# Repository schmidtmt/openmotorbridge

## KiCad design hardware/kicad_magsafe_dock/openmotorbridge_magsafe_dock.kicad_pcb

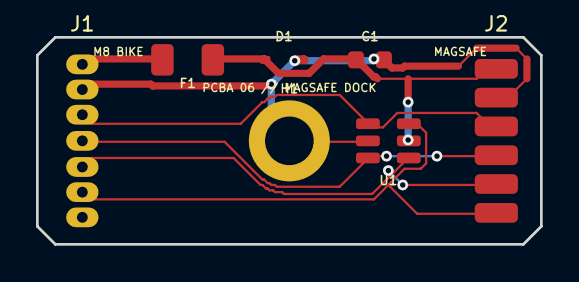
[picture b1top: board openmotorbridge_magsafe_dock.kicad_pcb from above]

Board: 2 copper layers, 28.0 x 11.5 mm, 7 parts (0 on the bottom side), 7 nets.

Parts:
C1: 100nF; C_0603_1608Metric
D1: ESD5Z5.0; D_SOD-323
F1: 500mA_PPTC; Fuse_1206_3216Metric
H1: M2.5_MOUNT_HOLE; MountingHole_2.7mm_M2.5_Pad
J1: M8_6P_WIRE_PADS; SolderWirePad_1x07_SMD_2.0mm
J2: MAGSAFE_6P_DOCK; PinHeader_1x06_P2.54mm_Vertical_SMD_Pin1Left
U1: USBLC6-4SC6; SOT-23-6

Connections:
1WIRE_ID: J1.6, J2.6, U1.6
GND: C1.2, D1.2, H1.1, J1.2, J2.2, U1.2
SIG_N: J1.4, J2.4, U1.3
SIG_P: J1.3, J2.3, U1.1
TRIGGER_PPS: J1.5, J2.5, U1.4
VCC_IN: F1.1, J1.1
VCC_PROT: C1.1, D1.1, F1.2, J2.1, U1.5

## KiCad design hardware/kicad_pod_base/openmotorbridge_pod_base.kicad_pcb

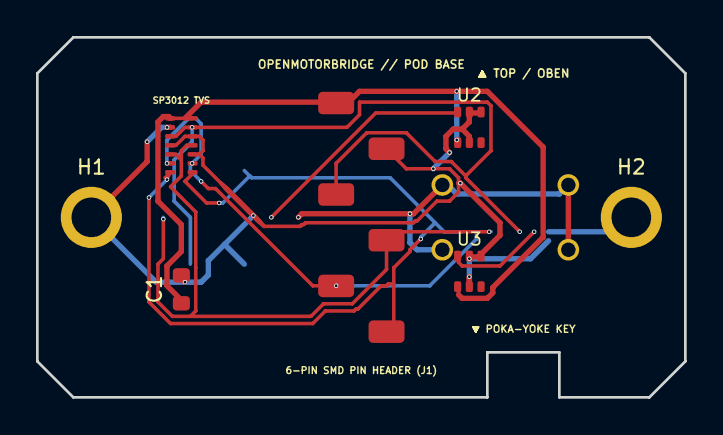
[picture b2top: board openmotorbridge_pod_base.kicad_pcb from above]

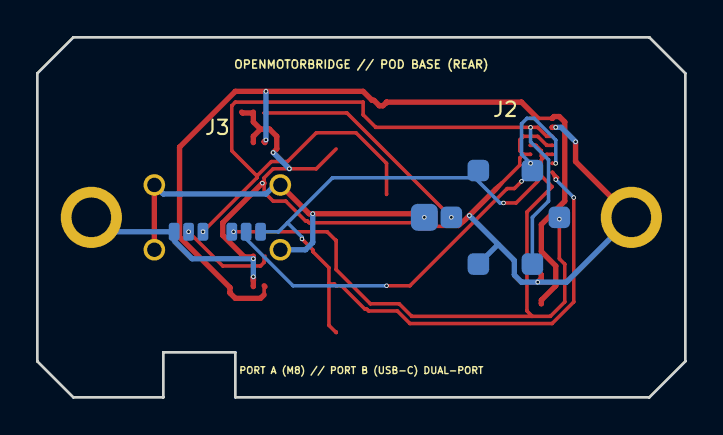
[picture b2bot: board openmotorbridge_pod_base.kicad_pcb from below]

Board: 2 copper layers, 36.0 x 20.0 mm, 9 parts (2 on the bottom side), 9 nets.

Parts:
C1: 100nF_50V; C_0603_1608Metric
H1, H2: M2_MountingHole; MountingHole_2.2mm_M2_Pad
J1: MILL_MAX_824_SMD_6P; PinHeader_1x06_P2.54mm_Vertical_SMD_Pin1Left
J2: PORT_A_M8_6PIN; M8_6Pin_IP67_Receptacle_Socketed
J3: PORT_B_USBC_VERTICAL; USB_C_Receptacle_Vertical_6P
U1: SP3012-06UTG; DFN-14_1.35x3.5mm_P0.5mm
U2: LM66100_PORTA; SOT-363_SC-70-6
U3: LM66100_PORTB; SOT-363_SC-70-6

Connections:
1WIRE_ID: J1.6, J2.6, J3.6, U1.7, U1.8
GND: C1.2, H1.1, H2.1, J1.2, J2.2, J3.1, U1.2, U1.4, U1.10, U1.12, U2.2, U2.3, U2.5, U3.2, U3.3, U3.5
GND_SHIELD: J2.7, J3.SH
SIG_N: J1.4, J2.4, J3.4, U1.5, U1.11
SIG_P: J1.3, J2.3, J3.3, U1.3, U1.13
TRIGGER_PPS: J1.5, J2.5, J3.5, U1.6, U1.9
VCC: C1.1, J1.1, U1.1, U1.14, U2.6, U3.6
VCC_M8: J2.1, U2.1
VCC_USBC: J3.2, U3.1

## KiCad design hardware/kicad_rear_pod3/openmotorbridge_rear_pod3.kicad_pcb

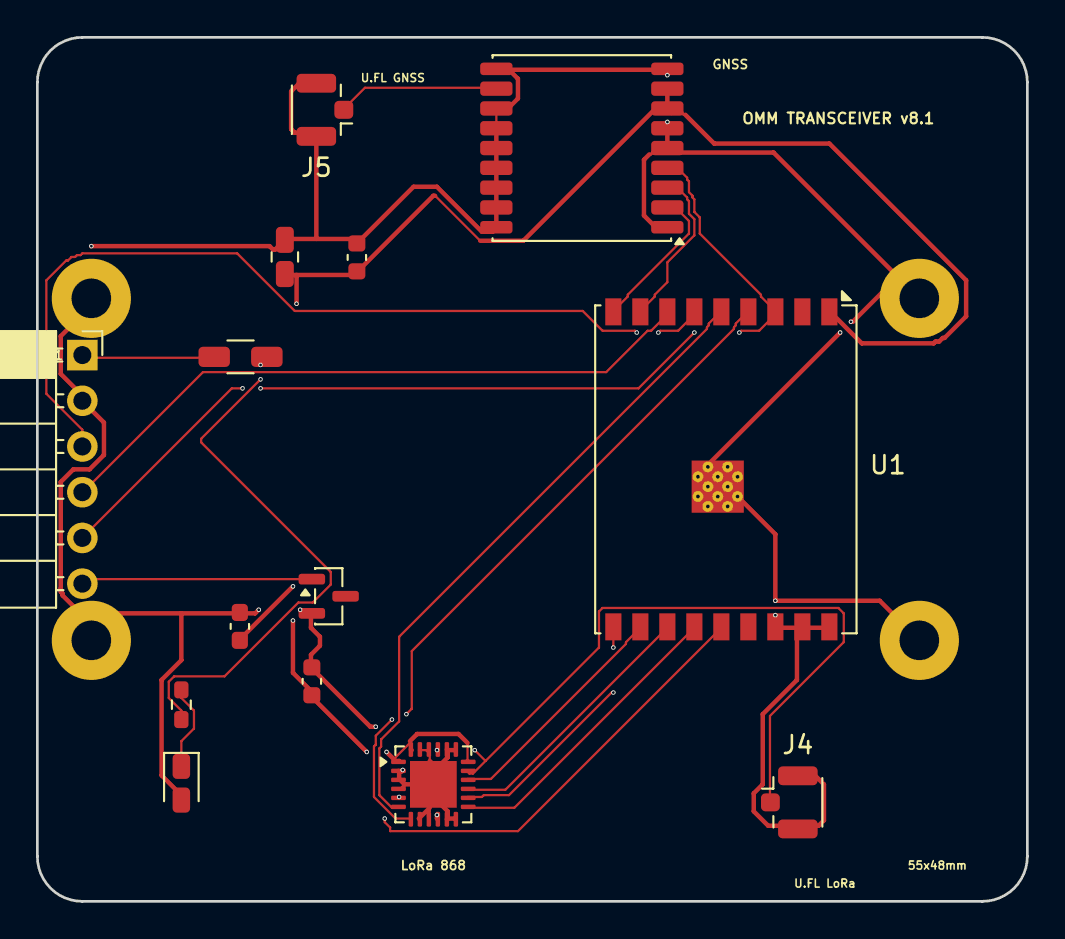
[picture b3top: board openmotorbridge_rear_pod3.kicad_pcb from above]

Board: 4 copper layers, 55.0 x 48.0 mm, 18 parts (0 on the bottom side), 20 nets.

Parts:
C1: 10uF_3V3; C_0805_2012Metric
C2: 100nF_MCU; C_0603_1608Metric
C3: 100nF_GNSS; C_0603_1608Metric
C4: 100nF_LoRa; C_0603_1608Metric
D1: LED_Green_5V; LED_0805_2012Metric
F1: PTC_500mA; R_1206_3216Metric
H1, H2, H3, H4: M2_Mounting_Hole; MountingHole_2.2mm_M2_Pad
J1: 6-Pin_OMM_Female_Socket; PinSocket_1x06_P2.54mm_Horizontal
J4: U.FL_LORA; U.FL_Hirose_U.FL-R-SMT-1_Vertical
J5: U.FL_GNSS; U.FL_Hirose_U.FL-R-SMT-1_Vertical
R1: 1.5k_LED_Resistor; R_0603_1608Metric
U1: ESP32-C3-WROOM-02U
U2: MAX-M10S_GNSS; ublox_MAX
U3: SX1262_LoRa_+22dBm; QFN-24-1EP_4x4mm_P0.5mm_EP2.6x2.6mm
U4: DS2401_1Wire_ID; SOT-23

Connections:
GND: C1.2, C2.2, C3.2, C4.2, D1.2, H1.1, H2.1, H3.1, H4.1, J1.2, J4.2, J5.2, U1.16, U1.17, U1.18, U1.19, U2.1, U2.5, U2.6, U2.9, U2.10, U2.12, U2.13, U2.14, U2.15, U2.16, U2.17, U2.18, U3.2, U3.3, U3.4, U3.8, U3.9, U3.11, U3.12, U3.19, U3.20, U3.22, U3.23, U3.25, U4.2
GNSS_1PPS: J1.5, U1.3, U2.4
GNSS_RF_IN: J5.1, U2.11
GNSS_RXD: U1.8, U2.3
GNSS_TXD: U1.9, U2.2
LORA_BUSY: U1.5, U3.6
LORA_DIO1: U1.4, U3.7
LORA_MISO: U1.11, U3.16
LORA_MOSI: U1.12, U3.15
LORA_NRST: U1.14, U3.5
LORA_NSS: U1.13, U3.13
LORA_RF_ANT: J4.1, U3.17, U3.21
LORA_SCK: U1.10, U3.14
NET_F1_5V: F1.2, R1.1
NET_LED_R: D1.1, R1.2
POD3_1WIRE_ID: J1.6, U4.1
POD3_UART_RX: J1.4, U1.7
POD3_UART_TX: J1.3, U1.6
POD3_VCC_5V: F1.1, J1.1
VCC_3V3: C1.1, C2.1, C3.1, C4.1, U1.1, U2.7, U2.8, U3.1, U3.10, U3.18, U3.24
